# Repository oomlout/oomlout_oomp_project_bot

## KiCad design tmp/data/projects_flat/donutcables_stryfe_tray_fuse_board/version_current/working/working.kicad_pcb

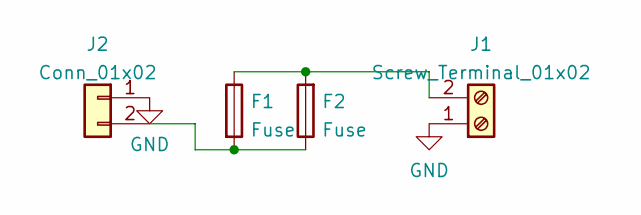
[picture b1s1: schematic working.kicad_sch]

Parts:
F1: Fuse; Fuseholder_Blade_ATO_Littelfuse_Pudenz_2_Pin
F2: Fuse; Fuseholder_Blade_Mini_Keystone_3568
J1: Screw_Terminal_01x02; Amass_XT60PW-M_Kombifootprint
J2: Conn_01x02; Amass_XT60PW-M_Kombifootprint

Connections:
GND: J1.1, J2.1
unnamed: F1.2, F2.1, J2.2
unnamed: F1.1, F2.2, J1.2

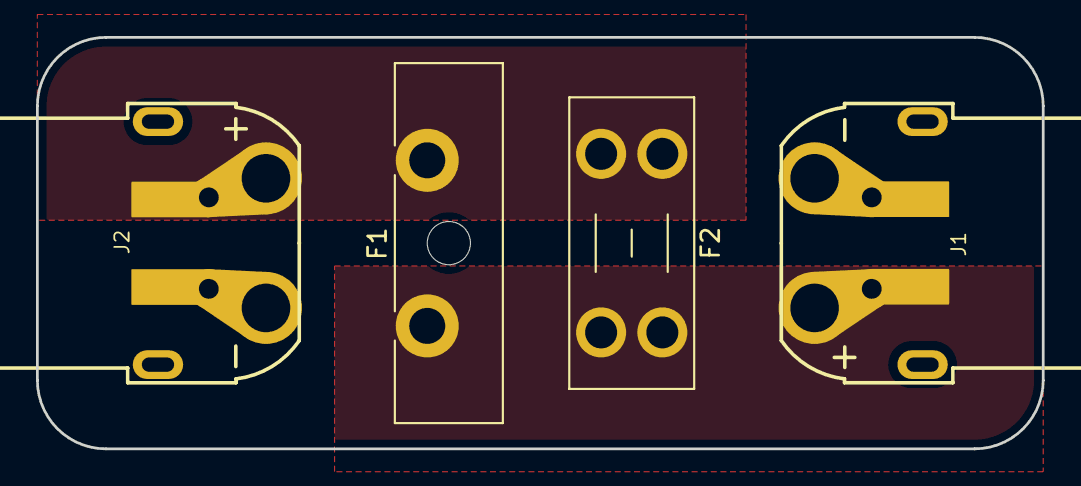
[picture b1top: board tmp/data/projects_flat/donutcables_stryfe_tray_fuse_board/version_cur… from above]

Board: 2 copper layers, 55.9 x 22.9 mm, 4 parts (0 on the bottom side), 3 nets.

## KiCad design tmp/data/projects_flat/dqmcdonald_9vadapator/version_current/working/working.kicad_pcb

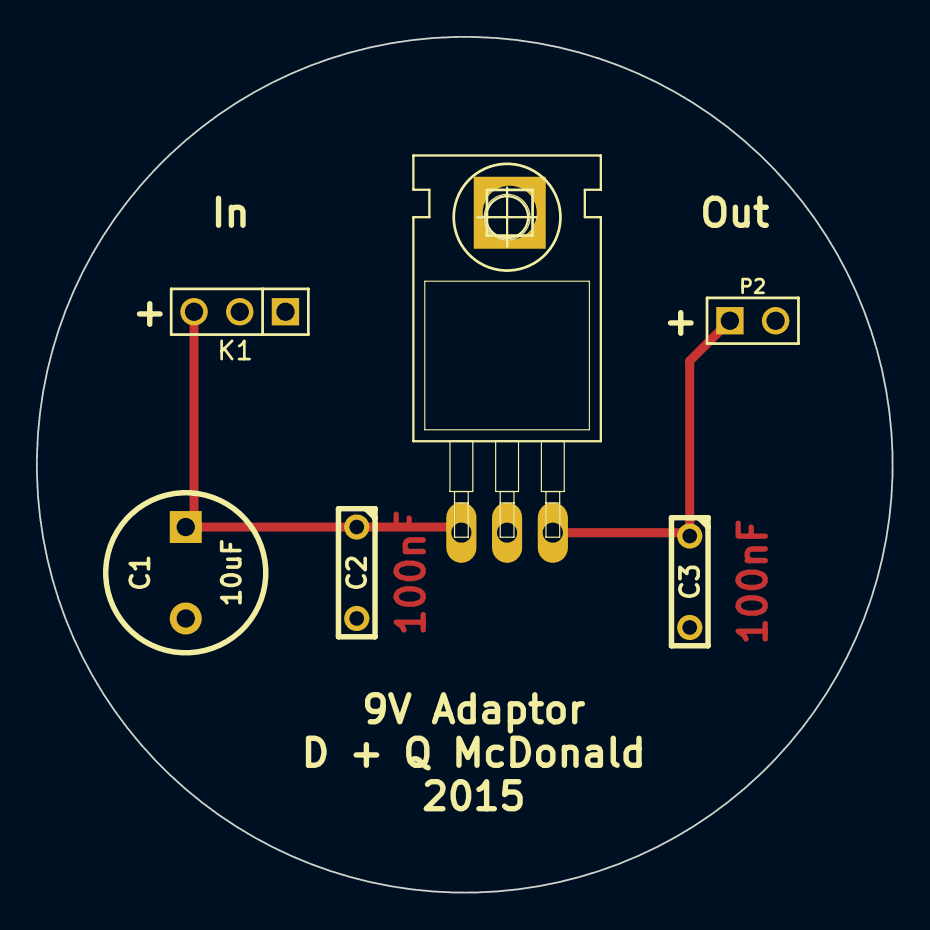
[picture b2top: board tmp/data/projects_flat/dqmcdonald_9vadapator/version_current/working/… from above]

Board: 2 copper layers, 47.5 x 47.5 mm, 6 parts (0 on the bottom side), 3 nets.

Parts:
C1: 10uF; C2V8
C2, C3: 0.1uF; C2
K1: CONN_3; PIN_ARRAY_3X1
P2: CONN_2; PIN_ARRAY_2X1
U1: LM7809ACT; -TO220

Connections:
unnamed: C1.1, C2.1, K1.3, U1.1
unnamed: C1.2, C2.2, C3.2, K1.1, P2.2, U1.2
unnamed: C3.1, P2.1, U1.3

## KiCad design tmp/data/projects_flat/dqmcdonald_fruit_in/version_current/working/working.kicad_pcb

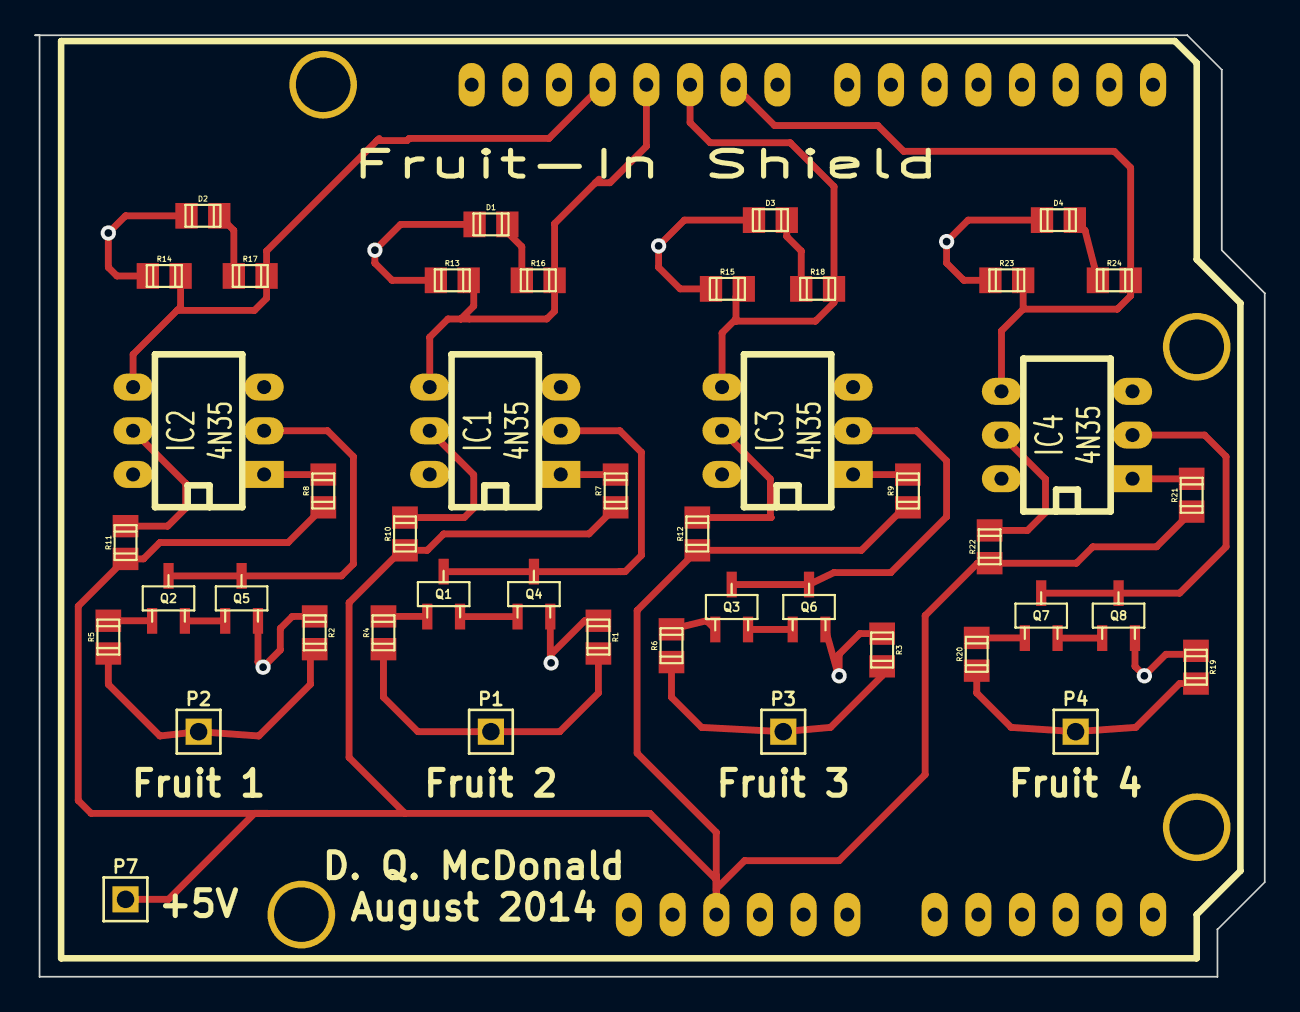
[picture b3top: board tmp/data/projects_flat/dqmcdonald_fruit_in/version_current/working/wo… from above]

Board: 2 copper layers, 71.5 x 54.8 mm, 45 parts (0 on the bottom side), 34 nets.

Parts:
D1, D2, D3, D4: LED; c_0805
IC1, IC2, IC3, IC4: 4N35; DIP-6__300_ELL
P1, P2, P3, P4, P7: CONN_1; PIN_ARRAY_1
Q1, Q2, Q3, Q4, Q5, Q6, Q7, Q8: 2N3904; sot23
R1, R2, R3, R19: 2.2M; c_0805
R4, R5, R6, R13, R14, R15, R20, R23: 10K; c_0805
R7, R8, R9, R10, R11, R12, R21, R22: 220 Ohms; c_0805
R16, R17, R18, R24: 470 Ohms; c_0805

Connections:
+5V: P7.1, R7.2, R8.2, R9.2, R10.2, R11.2, R12.2, R21.2, R22.2
D9: IC4.4, R23.1, R24.1
D10: IC3.4, R15.1, R18.1
D11: IC1.4, R13.1, R16.1
D12: IC2.4, R14.1, R17.1
GND: D1.2, D2.2, D3.2, D4.2, Q4.1, Q5.1, Q6.1, Q8.1, R1.2, R2.2, R3.2, R13.2, R14.2, R15.2, R19.2, R23.2
unnamed: D1.1, R16.2
unnamed: D2.1, R17.2
unnamed: D3.1, R18.2
unnamed: D4.1, R24.2
unnamed: IC1.1, R7.1
unnamed: IC1.2, Q1.3, Q4.3
unnamed: IC1.5, R10.1
unnamed: IC2.1, R8.1
unnamed: IC2.2, Q2.3, Q5.3
unnamed: IC2.5, R11.1
unnamed: IC3.1, R9.1
unnamed: IC3.2, Q3.3, Q6.3
unnamed: IC3.5, R12.1
unnamed: IC4.1, R21.1
unnamed: IC4.2, Q7.3, Q8.3
unnamed: IC4.5, R22.1
unnamed: P1.1, R1.1, R4.2
unnamed: P2.1, R2.1, R5.2
unnamed: P3.1, R3.1, R6.2
unnamed: P4.1, R19.1, R20.2
unnamed: Q1.1, Q4.2
unnamed: Q1.2, R4.1
unnamed: Q2.1, Q5.2
unnamed: Q2.2, R5.1
unnamed: Q3.1, Q6.2
unnamed: Q3.2, R6.1
unnamed: Q7.1, Q8.2
unnamed: Q7.2, R20.1

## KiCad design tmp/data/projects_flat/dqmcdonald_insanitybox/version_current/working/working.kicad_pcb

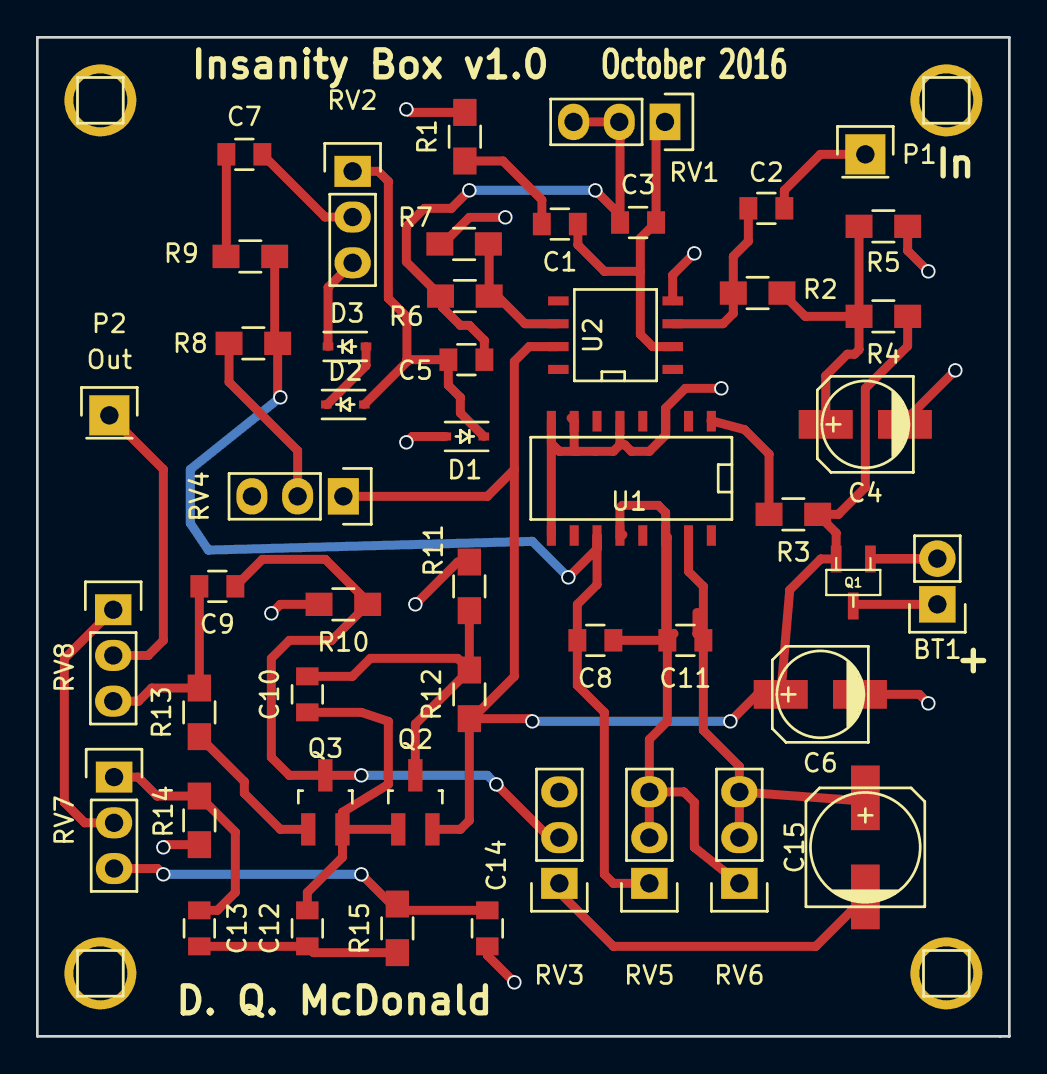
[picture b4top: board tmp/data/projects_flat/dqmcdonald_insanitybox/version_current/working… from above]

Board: 2 copper layers, 54.0 x 55.5 mm, 49 parts (0 on the bottom side), 29 nets.

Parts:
BT1: BATTERY; Pin_Header_Straight_1x02
C1: 0.47uF; C_0805
C2, C13: 0.01uF; C_0805
C3, C8, C11: 220pF; C_0805
C4, C6: 22uF; c_elec_5x5.3
C5, C7, C10, C12: 0.1uF; C_0805
C9: 24pF; C_0805
C14: 0.02uF; C_0805
C15: 10uF; c_elec_6.3x5.7
D1, D2, D3: 1N914; SOD-323
P1: CONN_1; Pin_Header_Straight_1x01
P2: Out; Pin_Header_Straight_1x01
Q1: MOSFET_P; pChannelMostfetSot23
Q2, Q3: FET_N; SOT-23_J201_JFET
R1: 4.7K; R_0805_HandSoldering
R2: 470K; R_0805_HandSoldering
R3: 200R; R_0805_HandSoldering
R4, R5: 10K; R_0805_HandSoldering
R6: 1.1K; R_0805_HandSoldering
R7: 100R; R_0805_HandSoldering
R8: 6.8K; R_0805_HandSoldering
R9, R10, R11, R12: 1M; R_0805_HandSoldering
R13: 1K; R_0805_HandSoldering
R14: 100K; R_0805_HandSoldering
R15: 39K; R_0805_HandSoldering
RV1: 1M; Pin_Header_Straight_1x03
RV2, RV3, RV5, RV6, RV7, RV8: 100K; Pin_Header_Straight_1x03
RV4: 50K; Pin_Header_Straight_1x03
U1: 4049; SO-16-N
U2: TL071; SOIC-8-N

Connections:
CMOS: C15.2, RV3.1
G071: BT1.2, C4.2, C6.2, C9.2, C14.2, D1.2, D3.1, Q1.G, R1.2, R5.2, R6.2, R10.2, R11.2, R13.2, R14.1, RV2.3, RV3.3, RV4.3, RV8.3, U1.3, U1.5, U1.7, U1.8, U1.9, U2.4
unnamed: BT1.1, Q1.D
unnamed: C1.1, C3.2, RV1.1, U2.2
unnamed: C1.2, R1.1
unnamed: C2.1, R2.1, U2.3
unnamed: C2.2, P1.1
unnamed: C3.1, C5.2, R7.1, RV1.2, RV1.3
unnamed: C5.1, D1.1, D2.2, RV2.1
unnamed: C7.1, R8.2
unnamed: C7.2, RV2.2
unnamed: C8.2, R8.1, R9.2, RV5.1, U1.11
unnamed: C9.1, Q3.G, R10.1, RV3.2
unnamed: C10.1, C12.2, Q2.S, Q3.D
unnamed: C10.2, Q2.G, R11.1, R12.2
unnamed: C11.1, C15.1, RV6.2, RV6.3, U1.15
unnamed: C8.1, C11.2, RV5.2, RV5.3, RV6.1, U1.12, U1.14
unnamed: C12.1, C13.2, R15.1
unnamed: C13.1, R14.2, RV7.1
unnamed: C14.1, R15.2, RV7.3
unnamed: D2.1, D3.2
unnamed: P2.1, RV8.2
unnamed: Q3.S, R13.1
unnamed: R6.1, R7.2, U2.6
unnamed: R9.1, RV4.2
unnamed: RV7.2, RV8.1
V071: C6.1, Q1.S, Q2.D, R3.1, R4.1, R12.1, RV4.1, U2.7
V4049: R3.2, U1.1
VR: C4.1, R2.2, R4.2, R5.1

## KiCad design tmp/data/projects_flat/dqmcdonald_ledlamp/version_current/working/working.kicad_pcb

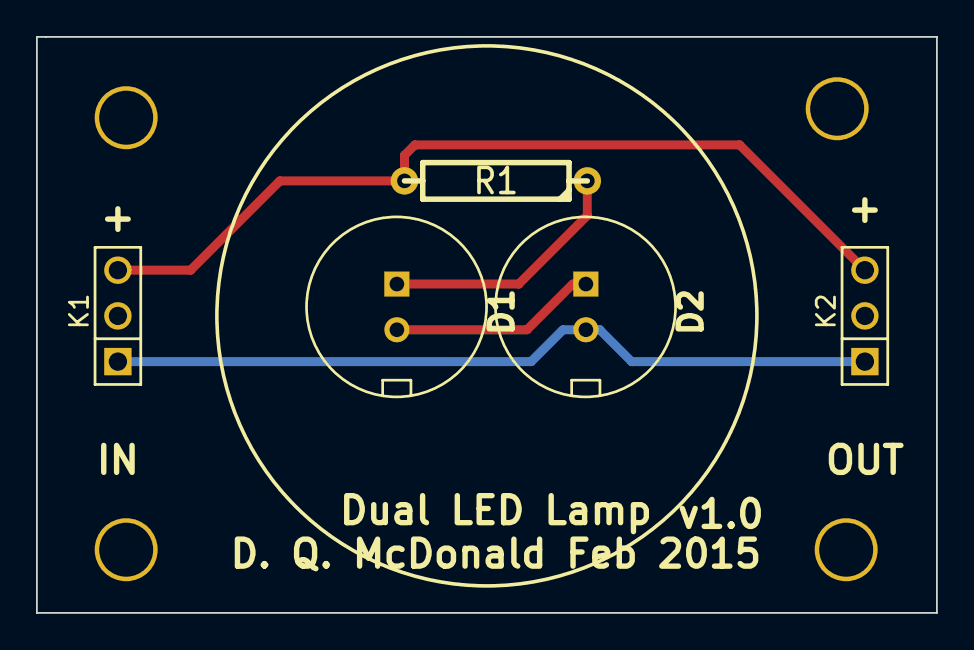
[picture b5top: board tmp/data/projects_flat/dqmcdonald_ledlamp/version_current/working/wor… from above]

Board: 2 copper layers, 50.0 x 32.0 mm, 5 parts (0 on the bottom side), 4 nets.

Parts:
D1, D2: LED; LED10mm
K1, K2: CONN_3; PIN_ARRAY_3X1
R1: 180 Ohm; R4

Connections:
unnamed: D1.1, R1.1
unnamed: D1.2, D2.1
unnamed: D2.2, K1.1, K2.1
unnamed: K1.3, K2.3, R1.2

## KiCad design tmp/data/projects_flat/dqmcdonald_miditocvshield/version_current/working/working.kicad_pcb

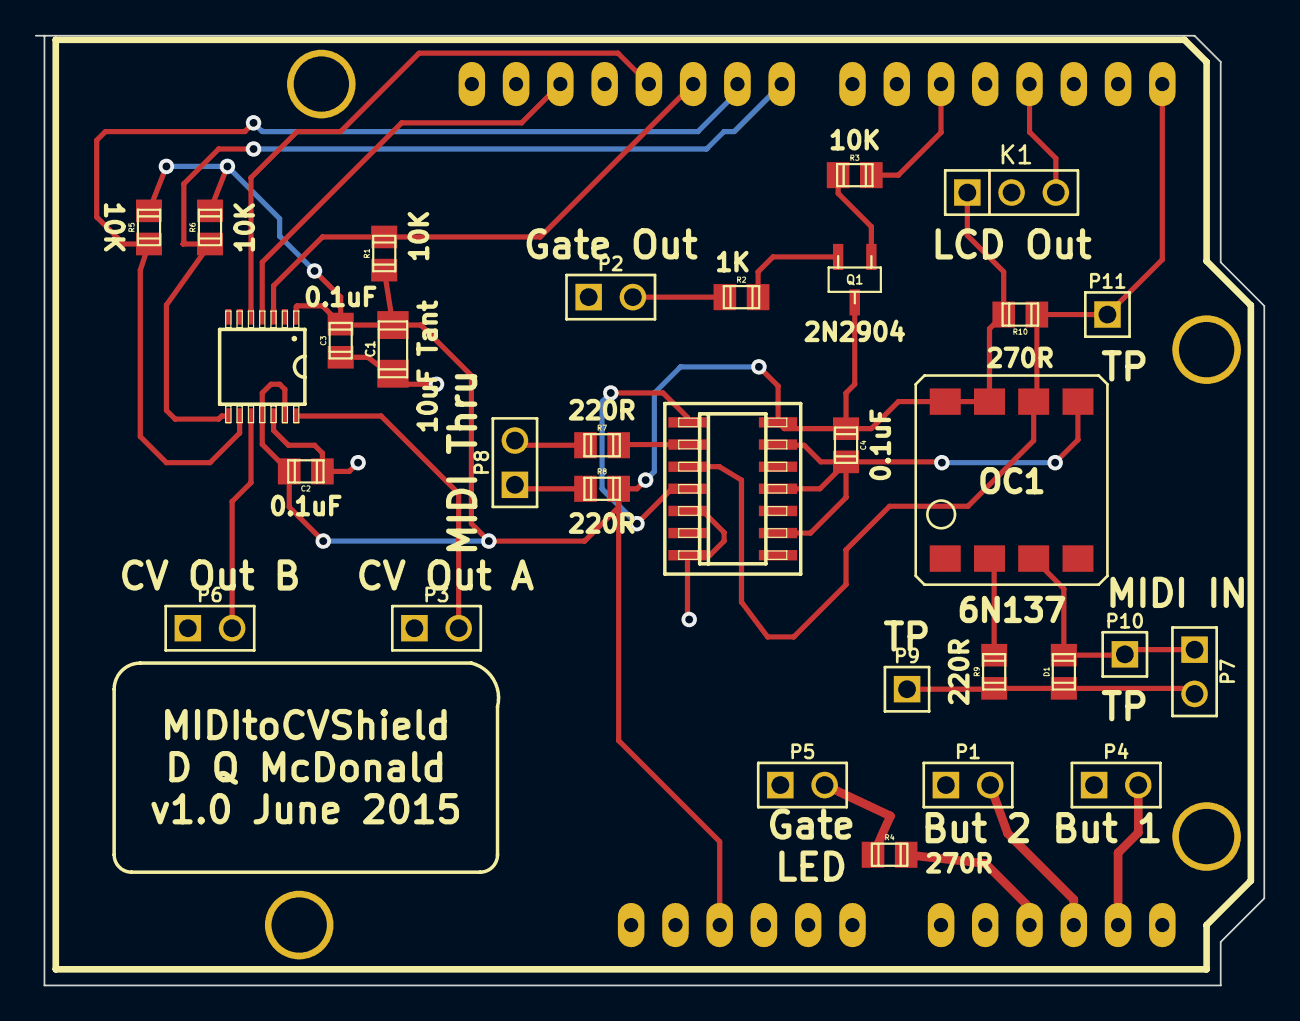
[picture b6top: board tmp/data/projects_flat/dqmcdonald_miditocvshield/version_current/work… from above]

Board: 2 copper layers, 70.0 x 54.5 mm, 31 parts (0 on the bottom side), 19 nets.

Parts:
C1: 10uF tant; c_1206
C2, C3, C4: 0.1uF; c_0805
D1: DIODE; c_0805
K1: CONN_3; PIN_ARRAY_3X1
OC1: 6N137
P1, P2, P3, P4, P5, P6, P7, P8: CONN_2; PIN_ARRAY_2X1
P9, P10, P11: CONN_1; PIN_ARRAY_1
Q1: NPN; sot23
R1, R3, R5, R6: 10K; c_0805
R2: 1K; c_0805
R4, R10: 270R; c_0805
R7, R8, R9: 220R; c_0805
U1: MCP4922
U2: 74LS14; -SO-14

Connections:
GND: C1.2, C2.2, C3.2, C4.1, K1.2, OC1.5, P1.1, P2.1, P3.1, P4.1, P5.1, P6.1, U1.12, U2.5, U2.7, U2.9, U2.11, U2.13
LDAC: R6.2, U1.8
unnamed: D1.1, OC1.3, P7.1, P10.1
unnamed: D1.2, P7.2, P9.1, R9.2
unnamed: OC1.2, R9.1
unnamed: P2.2, R2.2
unnamed: P5.2, R4.2
unnamed: P8.1, R8.2
unnamed: P8.2, R7.2
unnamed: Q1.1, R2.1
unnamed: Q1.2, R3.2
unnamed: R7.1, U2.2
unnamed: U2.1, U2.4
OUTA: P3.2, U1.14
OUTB: P6.2, U1.10
RX: OC1.6, P11.1, R10.2, U2.3
SHDN: R5.2, U1.9
SS: R1.1, U1.3
VDD: C1.1, C2.1, C3.1, C4.2, K1.1, OC1.7, OC1.8, Q1.3, R1.2, R5.1, R6.1, R8.1, R10.1, U1.1, U1.11, U1.13, U2.14

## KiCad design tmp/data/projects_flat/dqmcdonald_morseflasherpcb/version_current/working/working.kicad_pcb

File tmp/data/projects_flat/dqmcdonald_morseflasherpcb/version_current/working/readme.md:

# MorseFlasherPCB by dqmcdonald  
This is a harvested standardized copy of a project from github.  
The original project can be found at:  
https://github.com/dqmcdonald/MorseFlasherPCB  
Please consult that link for additional, details, files, and license information.  
Note: It was auto harvested and if the original repo had more than one board file or anything out of the ordinary the files here are likely not representative.

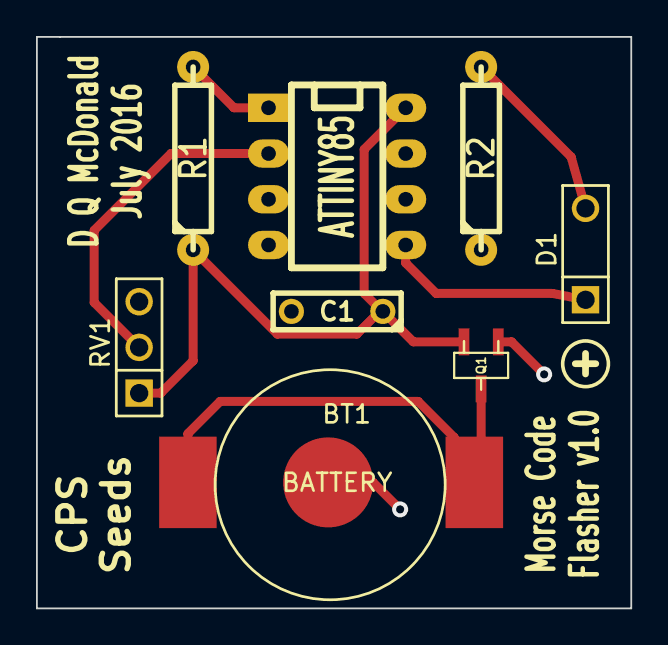
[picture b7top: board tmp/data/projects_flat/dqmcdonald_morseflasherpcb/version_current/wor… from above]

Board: 2 copper layers, 33.0 x 31.8 mm, 8 parts (0 on the bottom side), 7 nets.

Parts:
BT1: BATTERY; Coin_Cell_12mm_SMD
C1: 100nF; C2
D1: LED; TwinScrewTerminal
Q1: MOSFET_P; pChannelMostfetSot23
R1: 10K; R4-LARGE_PADS
R2: 120K; R4-LARGE_PADS
RV1: POT; PIN_ARRAY_3X1
U1: ATTINY85; DIP-8__300_ELL

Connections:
GND: BT1.2, C1.2, Q1.G, R2.1, RV1.3, U1.4
unnamed: BT1.1, Q1.D
unnamed: D1.1, U1.5
unnamed: D1.2, R2.2
unnamed: R1.2, U1.1
unnamed: RV1.2, U1.2
VCC: C1.1, Q1.S, R1.1, RV1.1, U1.8

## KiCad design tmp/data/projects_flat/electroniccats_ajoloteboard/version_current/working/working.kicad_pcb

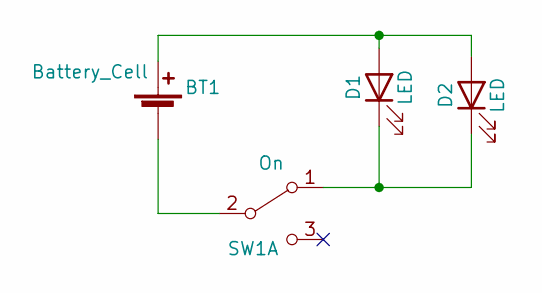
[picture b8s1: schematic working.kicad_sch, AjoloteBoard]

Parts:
BT1: Battery_Cell; BAT-HLD-001
D1, D2: LED; LED_D5.0mm_Clear
SW1: On; JS102011SAQN

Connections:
unnamed: BT1.2 (+), D1.2 (A), D2.2 (A)
unnamed: BT1.1 (-), SW1.2 (B)
unnamed: D1.1 (K), D2.1 (K), SW1.1 (A)

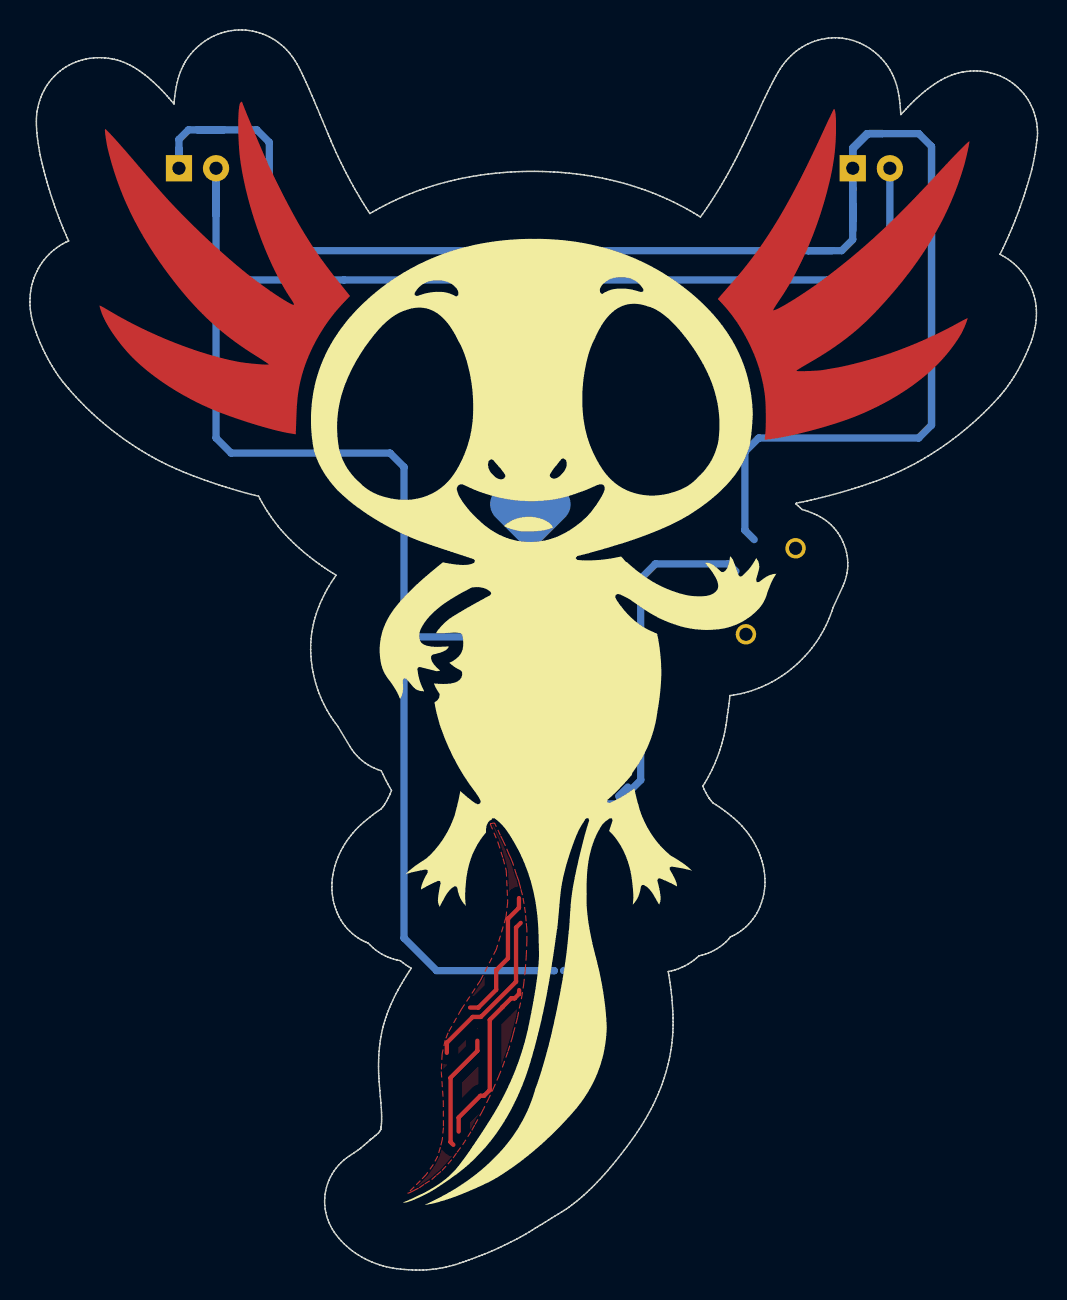
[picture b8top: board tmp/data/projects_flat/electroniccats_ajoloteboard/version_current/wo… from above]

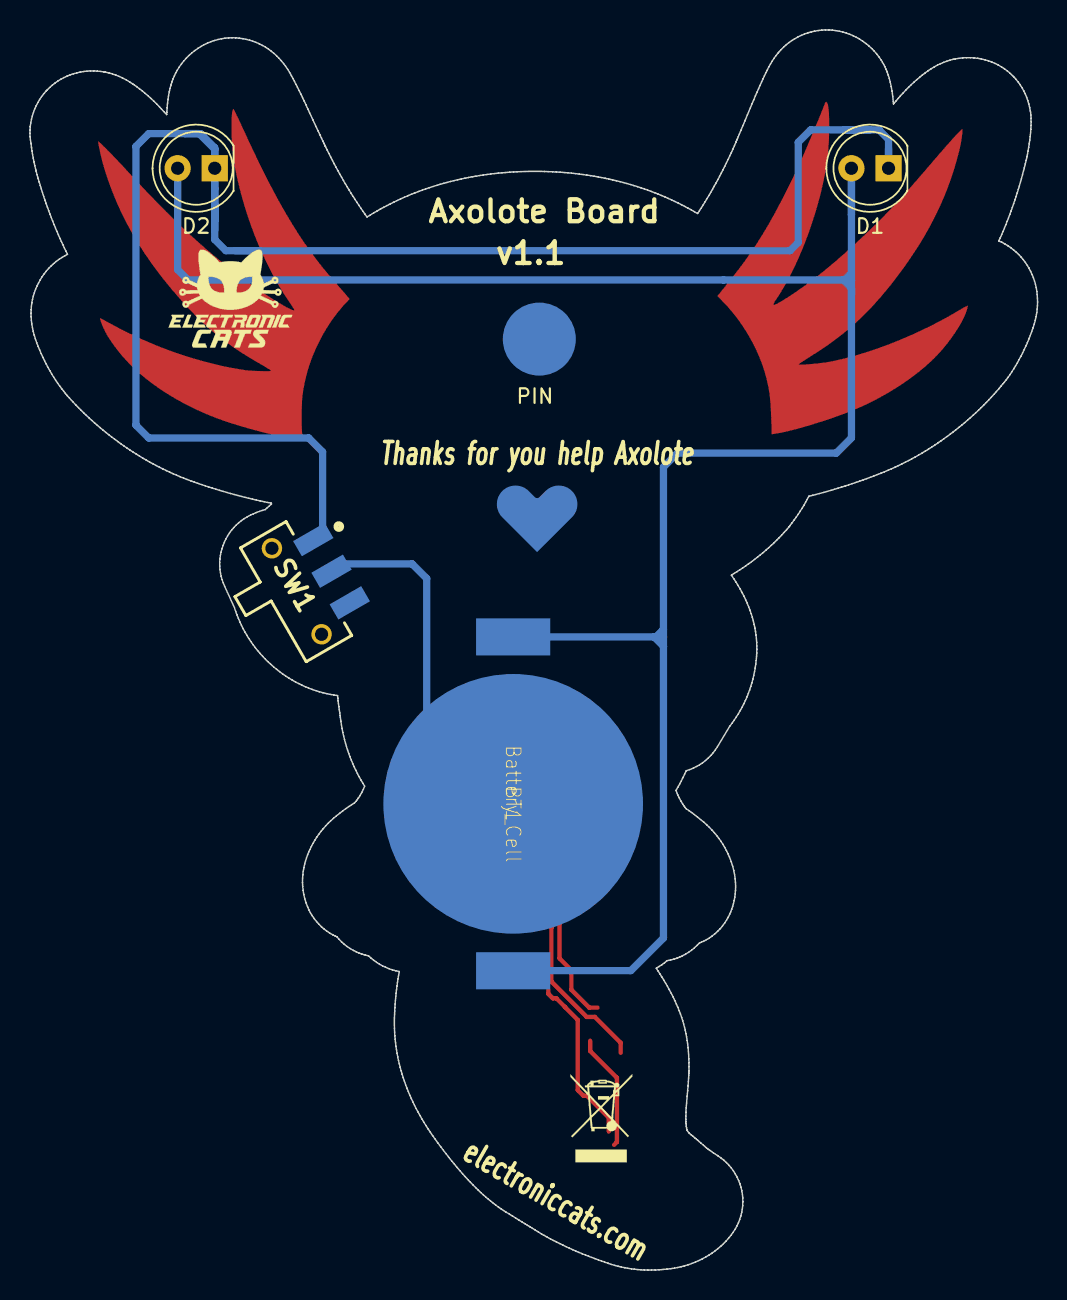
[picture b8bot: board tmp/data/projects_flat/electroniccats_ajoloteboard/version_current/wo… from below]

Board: 2 copper layers, 69.0 x 84.9 mm, 7 parts (6 on the bottom side), 3 nets.

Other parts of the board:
PIN: Tacks_tachuelas
svg2mod: ajolote; svg2mod
svg2mod#2: G***; heart
